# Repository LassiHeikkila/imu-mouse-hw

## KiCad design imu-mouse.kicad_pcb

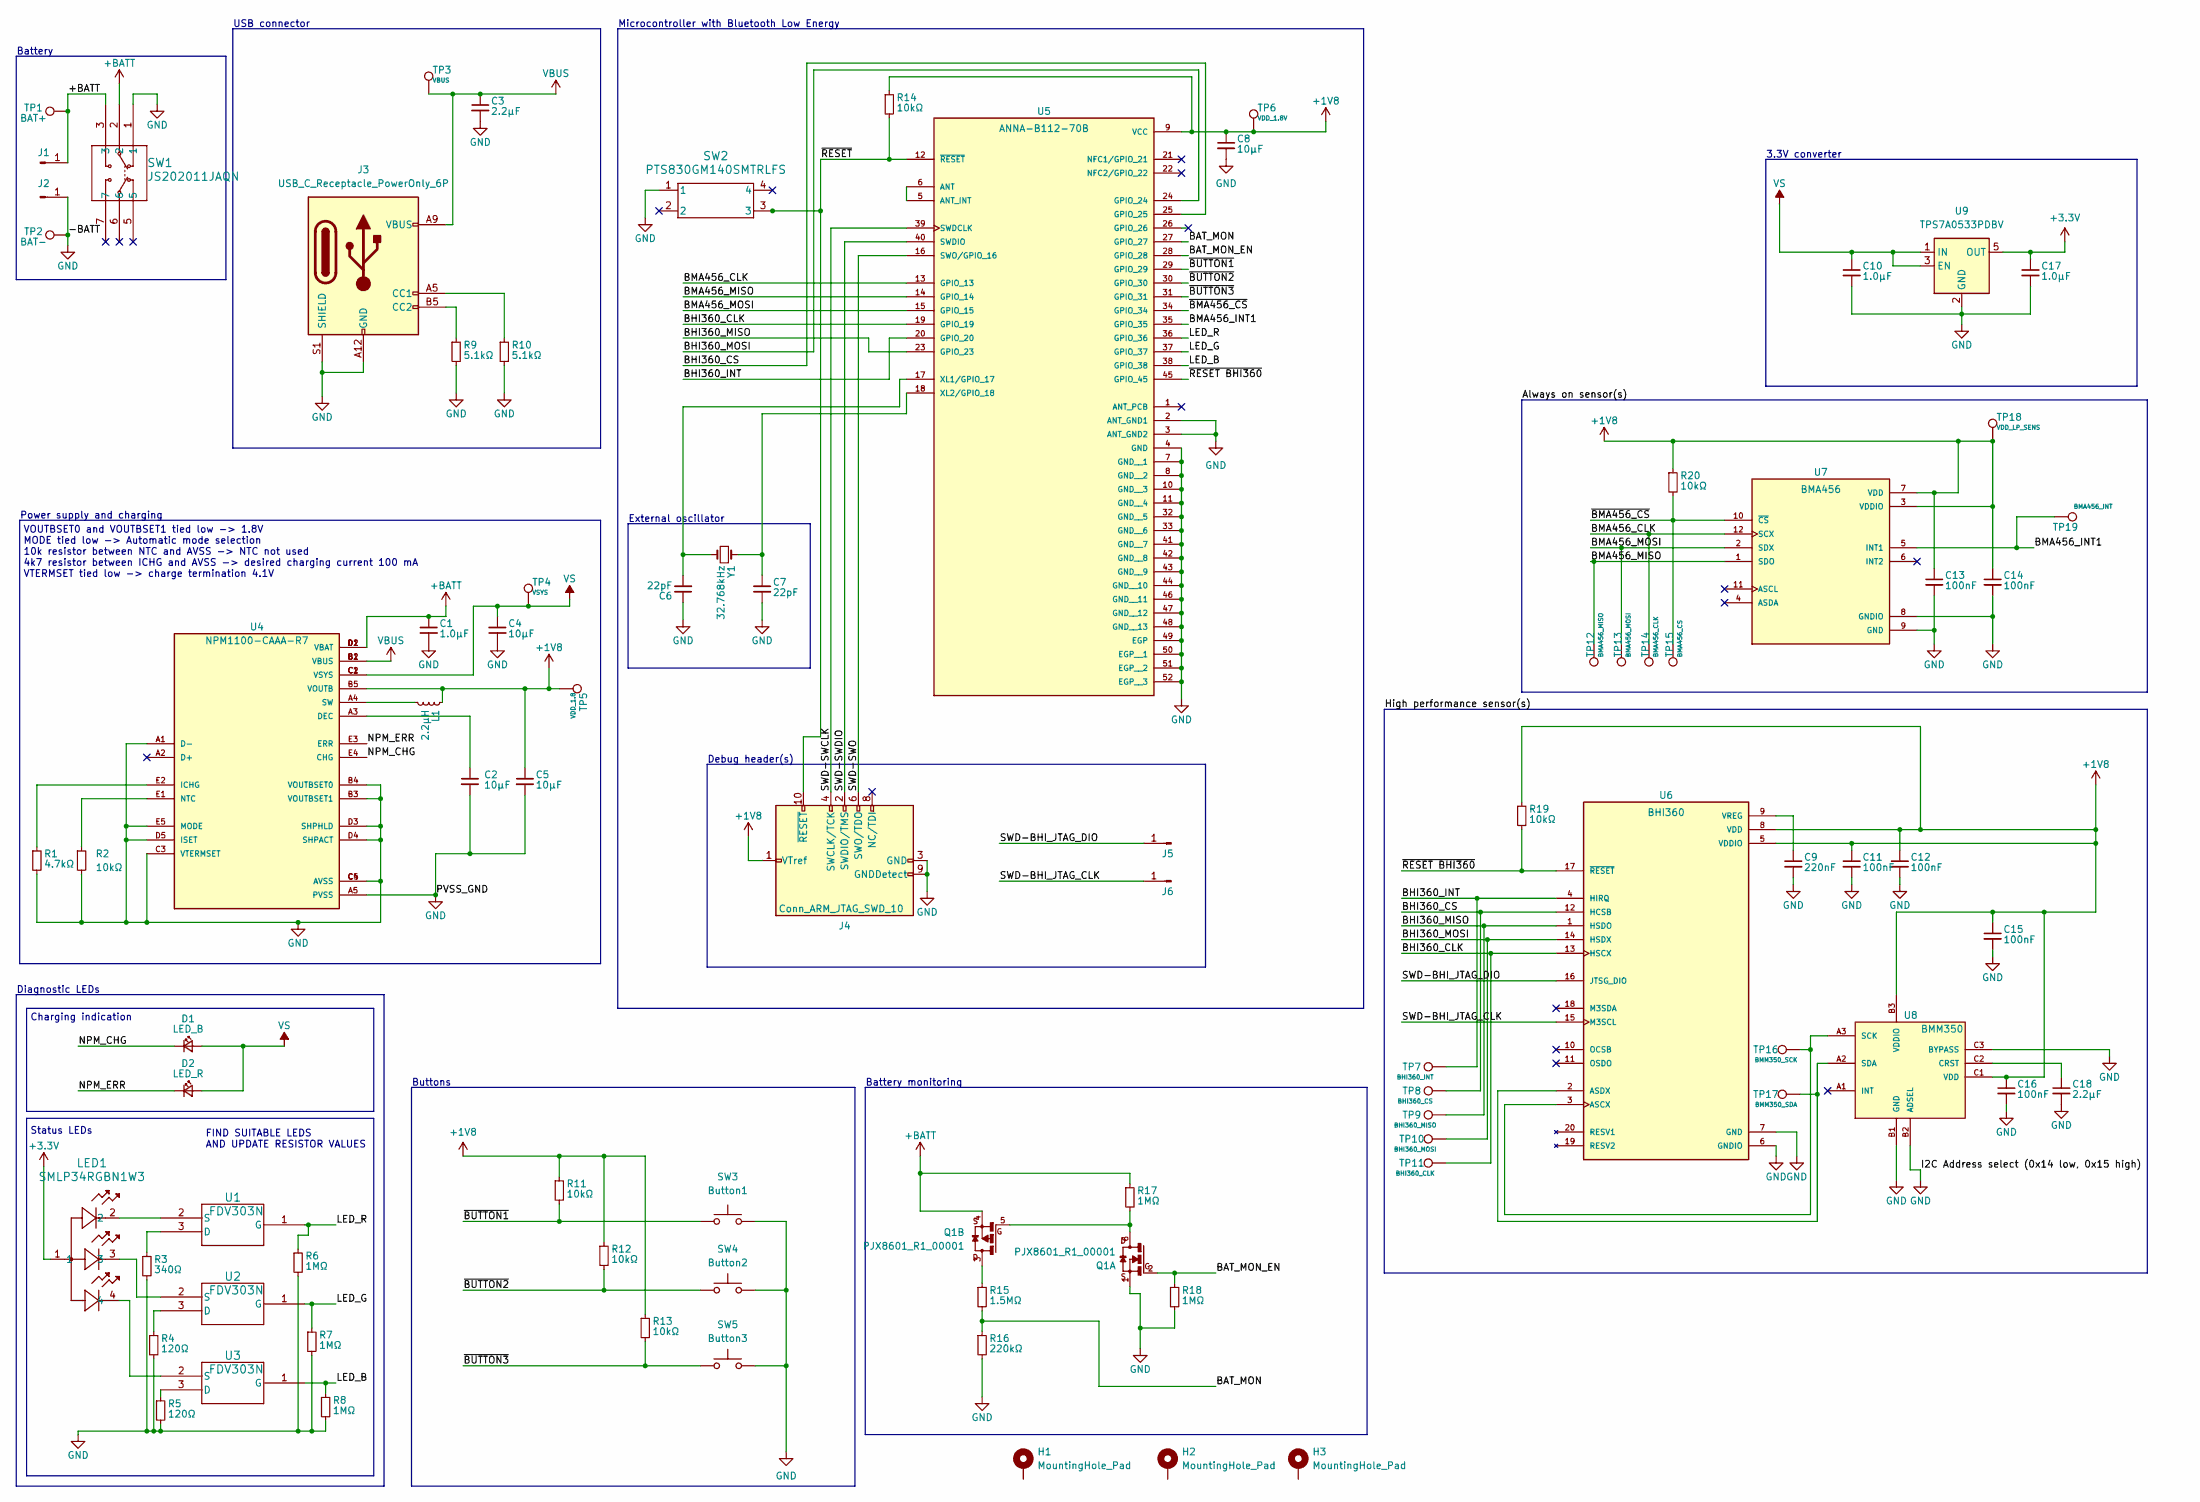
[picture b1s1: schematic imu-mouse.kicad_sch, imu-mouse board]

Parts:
C1, C10, C17: 1.0µF; C_0805_2012Metric; DigiKey_Part_Number CC0805KKX7R8BB105
C2, C4, C5, C8: 10µF; C_0805_2012Metric; DigiKey_Part_Number CC0805KKX7R6BB106
C3, C18: 2.2µF; C_0805_2012Metric; DigiKey_Part_Number CC0805KRX5R7BB225
C6, C7: 22pF; C_0805_2012Metric; DigiKey_Part_Number CC0805KKX7R6BB106
C9: 220nF; C_0805_2012Metric; DigiKey_Part_Number CC0805KRX7R8BB224
C11, C12, C13, C14, C15, C16: 100nF; C_0805_2012Metric; DigiKey_Part_Number CC0805KRX7R9BB104
D1: LED_B; LED_0805_2012Metric; DigiKey_Part_Number 150080BS75000
D2: LED_R; LED_0805_2012Metric; DigiKey_Part_Number 150080RS75000
H1, H2, H3: MountingHole_Pad; MountingHole_3.5mm_Pad
J1, J2, J5, J6: Conn_01x01_Pin; SolderWire-0.1sqmm_1x01_D0.4mm_OD1mm
J3: USB_C_Receptacle_PowerOnly_6P; USB_C_Receptacle_GCT_USB4125-xx-x_6P_TopMnt_Horizontal; DigiKey_Part_Number USB4125-GF-A
J4: Conn_ARM_JTAG_SWD_10; PinHeader_2x05_P1.27mm_Vertical; DigiKey_Part_Number FTSH-105-01-L-DV-007-K
L1: 2.2µH; L_0805_2012Metric; DigiKey_Part_Number dfe201210u-2r2m-p2
LED1: SMLP34RGBN1W3; SMLP34_ROM; DigiKey_Part_Number SMLP34RGBN1W3
Q1: PJX8601_R1_00001; SOT50P160X60-6N; DigiKey_Part_Number PJX8601-R1-00001
R1: 4.7kΩ; R_0805_2012Metric; DigiKey_Part_Number RC0805FR-071K5L
R2, R11, R12, R13, R14, R19, R20: 10kΩ; R_0805_2012Metric; DigiKey_Part_Number RT0805FRE0710KL
R3: 340Ω; R_0805_2012Metric; DigiKey_Part_Number RC0805FR-07330RL
R4, R5: 120Ω; R_0805_2012Metric; DigiKey_Part_Number RT0805FRE07120RL
R6, R7, R8, R17, R18: 1MΩ; R_0805_2012Metric; DigiKey_Part_Number RC0805FR-071ML
R9, R10: 5.1kΩ; R_0805_2012Metric; DigiKey_Part_Number RC0805JR-075K1L
R15: 1.5MΩ; R_0805_2012Metric; DigiKey_Part_Number RT0805FRE071M5L
R16: 220kΩ; R_0805_2012Metric; DigiKey_Part_Number RT0805FRE07220KL
SW1: JS202011JAQN; DigiKey_Part_Number JS202011JAQN
SW2: PTS830GM140SMTRLFS; SWITCH_0SMTRLFS; DigiKey_Part_Number PTS830GM140-SMTR-LFS
SW3: Button1; SW_SPST_PTS645; DigiKey_Part_Number PTS645SL43SMTR92-LFS
SW4: Button2; SW_SPST_PTS645; DigiKey_Part_Number PTS645SL43SMTR92-LFS
SW5: Button3; SW_SPST_PTS645; DigiKey_Part_Number PTS645SL43SMTR92-LFS
TP1: BAT+; TestPoint_Pad_D1.0mm
TP2: BAT-; TestPoint_Pad_D1.0mm
TP3: VBUS; TestPoint_Pad_D1.0mm
TP4: VSYS; TestPoint_Pad_D1.0mm
TP5: VDD_1.8; TestPoint_Pad_D1.0mm
TP6: VDD_1.8V; TestPoint_Pad_D1.0mm
TP7: BHI360_INT; TestPoint_Pad_D1.0mm
TP8: BHI360_CS; TestPoint_Pad_D1.0mm
TP9: BHI360_MISO; TestPoint_Pad_D1.0mm
TP10: BHI360_MOSI; TestPoint_Pad_D1.0mm
TP11: BHI360_CLK; TestPoint_Pad_D1.0mm
TP12: BMA456_MISO; TestPoint_Pad_D1.0mm
TP13: BMA456_MOSI; TestPoint_Pad_D1.0mm
TP14: BMA456_CLK; TestPoint_Pad_D1.0mm
TP15: BMA456_CS; TestPoint_Pad_D1.0mm
TP16: BMM350_SCK; TestPoint_Pad_D1.0mm
TP17: BMM350_SDA; TestPoint_Pad_D1.0mm
TP18: VDD_LP_SENS; TestPoint_Pad_D1.0mm
TP19: BMA456_INT; TestPoint_Pad_D1.0mm
U1, U2, U3: FDV303N; SOT-23-3L_FAS; DigiKey_Part_Number FDV303N
U4: NPM1100-CAAA-R7; BGA25C40P5X5_207X207X52N; DigiKey_Part_Number npm1100-caab-r
U5: ANNA-B112-70B; XCVR_ANNA-B112-70B; DigiKey_Part_Number anna-b112-70b
U6: BHI360; XDCR_BHI360; DigiKey_Part_Number bhi360
U7: BMA456; XDCR_BMA456; DigiKey_Part_Number bma456
U8: BMM350; BGA9C40P3X3_128X128X50; DigiKey_Part_Number BMM350
U9: TPS7A0533PDBV; SOT-23-5; DigiKey_Part_Number TPS7A0533PDBVR
Y1: 32.768kHz; Crystal_SMD_2012-2Pin_2.0x1.2mm; DigiKey_Part_Number FC-12M-32-7680KD-A0

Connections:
+1V8: C5.1, C8.1, C11.1, C12.1, C13.1, C14.1, C15.1, C16.1, J4.1 (VTref), L1.1, R11.1, R12.1, R13.1, R14.1, R19.1, R20.1, TP5.1, TP6.1, TP18.1, U4.B5 (VOUTB), U5.9 (VCC), U6.5 (VDDIO), U6.8 (VDD), U7.3 (VDDIO), U7.7 (VDD), U8.B3 (VDDIO), U8.C1 (VDD); also elsewhere on the board
+3.3V: C17.1, LED1.1, U9.5 (OUT)
+BATT: C1.1, J1.1, Q1.4, R17.1, SW1.2, SW1.3, TP1.1, U4.D1 (VBAT), U4.D2 (VBAT)
/BAT_MON: R15.2, R16.1, U5.27 (GPIO_27); also elsewhere on the board
/BAT_MON_EN: Q1.2, R18.1, U5.28 (GPIO_28); also elsewhere on the board
/BHI360_CLK: TP11.1, U5.19 (GPIO_19), U6.13 (HSCX); also elsewhere on the board
/BHI360_CS: TP8.1, U5.25 (GPIO_25), U6.12 (HCSB); also elsewhere on the board
/BHI360_INT: TP7.1, U5.20 (GPIO_20), U6.4 (HIRQ); also elsewhere on the board
/BHI360_MISO: TP9.1, U5.23 (GPIO_23), U6.1 (HSDO); also elsewhere on the board
/BHI360_MOSI: TP10.1, U5.24 (GPIO_24), U6.14 (HSDX); also elsewhere on the board
/BMA456_CLK: TP14.1, U5.13 (GPIO_13), U7.12 (SCX); also elsewhere on the board
/BMA456_INT1: TP19.1, U5.35 (GPIO_35), U7.5 (INT1); also elsewhere on the board
/BMA456_MISO: TP12.1, U5.14 (GPIO_14), U7.1 (SDO); also elsewhere on the board
/BMA456_MOSI: TP13.1, U5.15 (GPIO_15), U7.2 (SDX); also elsewhere on the board
/LED_B: R8.1, U3.1 (G), U5.38 (GPIO_38); also elsewhere on the board
/LED_G: R7.1, U2.1 (G), U5.37 (GPIO_37); also elsewhere on the board
/LED_R: R6.1, U1.1 (G), U5.36 (GPIO_36); also elsewhere on the board
/NPM_CHG: D1.1 (K), U4.E4 (CHG)
/NPM_ERR: D2.1 (K), U4.E3 (ERR)
/SWD-BHI_JTAG_CLK: J6.1, U6.15 (M3SCL)
/SWD-BHI_JTAG_DIO: J5.1, U6.16 (JTSG_DIO)
/SWD-SWCLK: J4.4 (SWCLK/TCK), U5.39 (SWDCLK); also elsewhere on the board
/SWD-SWDIO: J4.2 (SWDIO/TMS), U5.40 (SWDIO); also elsewhere on the board
/SWD-SWO: J4.6 (SWO/TDO), U5.16 (SWO/GPIO_16); also elsewhere on the board
/~BMA456_CS: R20.2, TP15.1, U5.34 (GPIO_34), U7.10 (~CS); also elsewhere on the board
/~BUTTON1: R11.2, SW3.1, U5.29 (GPIO_29); also elsewhere on the board
/~BUTTON2: R12.2, SW4.1, U5.30 (GPIO_30); also elsewhere on the board
/~BUTTON3: R13.2, SW5.1, U5.31 (GPIO_31); also elsewhere on the board
/~RESET BHI360: R19.2, U5.45 (GPIO_45), U6.17 (~RESET); also elsewhere on the board
/~RESET: J4.10 (~RESET), R14.2, SW2.3, U5.12 (~RESET); also elsewhere on the board
GND: C1.2, C2.2, C3.2, C4.2, C5.2, C6.1, C7.2, C8.2, C9.2, C10.2, C11.2, C12.2, C13.2, C14.2, C15.2, C16.2, C17.2, C18.2, J2.1, J3.A12 (GND), J3.B12 (GND), J3.S1 (SHIELD), J4.3 (GND), J4.5 (GND), J4.9 (GNDDetect), Q1.1, R1.2, R2.2, R3.2, R4.2, R5.2, R6.2, R7.2, R8.2, R9.2, R10.2, R16.2, R18.2, SW1.1, SW2.1, SW3.2, SW4.2, SW5.2, TP2.1, U4.A1 (D-), U4.A5 (PVSS), U4.B3 (VOUTBSET1), U4.B4 (VOUTBSET0), U4.C3 (VTERMSET), U4.C4 (AVSS), U4.C5 (AVSS), U4.D3 (SHPHLD), U4.D4 (SHPACT), U4.D5 (ISET), U4.E5 (MODE), U5.2 (ANT_GND1), U5.3 (ANT_GND2), U5.4 (GND), U5.7 (GND__1), U5.8 (GND__2), U5.10 (GND__3), U5.11 (GND__4), U5.32 (GND__5), U5.33 (GND__6), U5.41 (GND__7), U5.42 (GND__8), U5.43 (GND__9), U5.44 (GND__10), U5.46 (GND__11), U5.47 (GND__12), U5.48 (GND__13), U5.49 (EGP), U5.50 (EGP__1), U5.51 (EGP__2), U5.52 (EGP__3), U6.6 (GNDIO), U6.7 (GND), U7.8 (GNDIO), U7.9 (GND), U8.B1 (GND), U8.B2 (ADSEL), U8.C3 (BYPASS), U9.2 (GND); also elsewhere on the board
unnamed: J3.A5 (CC1), R10.1
unnamed: J3.B5 (CC2), R9.1
unnamed: Q1.3, R15.1
unnamed: Q1.5, Q1.6, R17.2
unnamed: R3.1, U1.3 (D)
unnamed: LED1.2, U1.2 (S)
unnamed: R4.1, U2.3 (D)
unnamed: LED1.3, U2.2 (S)
unnamed: R5.1, U3.3 (D)
unnamed: LED1.4, U3.2 (S)
unnamed: C2.1, U4.A3 (DEC)
unnamed: R1.1, U4.E2 (ICHG)
unnamed: R2.1, U4.E1 (NTC)
unnamed: L1.2, U4.A4 (SW)
unnamed: U5.5 (ANT_INT), U5.6 (ANT)
unnamed 47: C6.2, U5.17 (XL1/GPIO_17), Y1.2; also elsewhere on the board
unnamed 48: C7.1, U5.18 (XL2/GPIO_18), Y1.1; also elsewhere on the board
unnamed: TP16.1, U6.3 (ASCX), U8.A3 (SCK)
unnamed: TP17.1, U6.2 (ASDX), U8.A2 (SDA)
unnamed: C9.1, U6.9 (VREG)
unnamed: C18.1, U8.C2 (CRST)
VBUS: C3.1, J3.A9 (VBUS), J3.B9 (VBUS), TP3.1, U4.B1 (VBUS), U4.B2 (VBUS)
VS: C4.1, C10.1, D1.2 (A), D2.2 (A), TP4.1, U4.C1 (VSYS), U4.C2 (VSYS), U9.1 (IN), U9.3 (EN)

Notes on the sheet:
USB connector
Microcontroller with Bluetooth Low Energy
Power supply and charging
External oscillator
VOUTBSET0 and VOUTBSET1 tied low -> 1.8V MODE tied low -> Automatic mode selection 10k resistor between NTC and AVSS -> NTC not used 4k7 resistor between ICHG and AVSS -> desired charging current 100 mA VTERMSET tied low -> charge termination 4.1V
FIND SUITABLE LEDS AND UPDATE RESISTOR VALUES
Diagnostic LEDs
Debug header(s)
Buttons
Battery monitoring
Status LEDs
Charging indication
Battery
3.3V converter

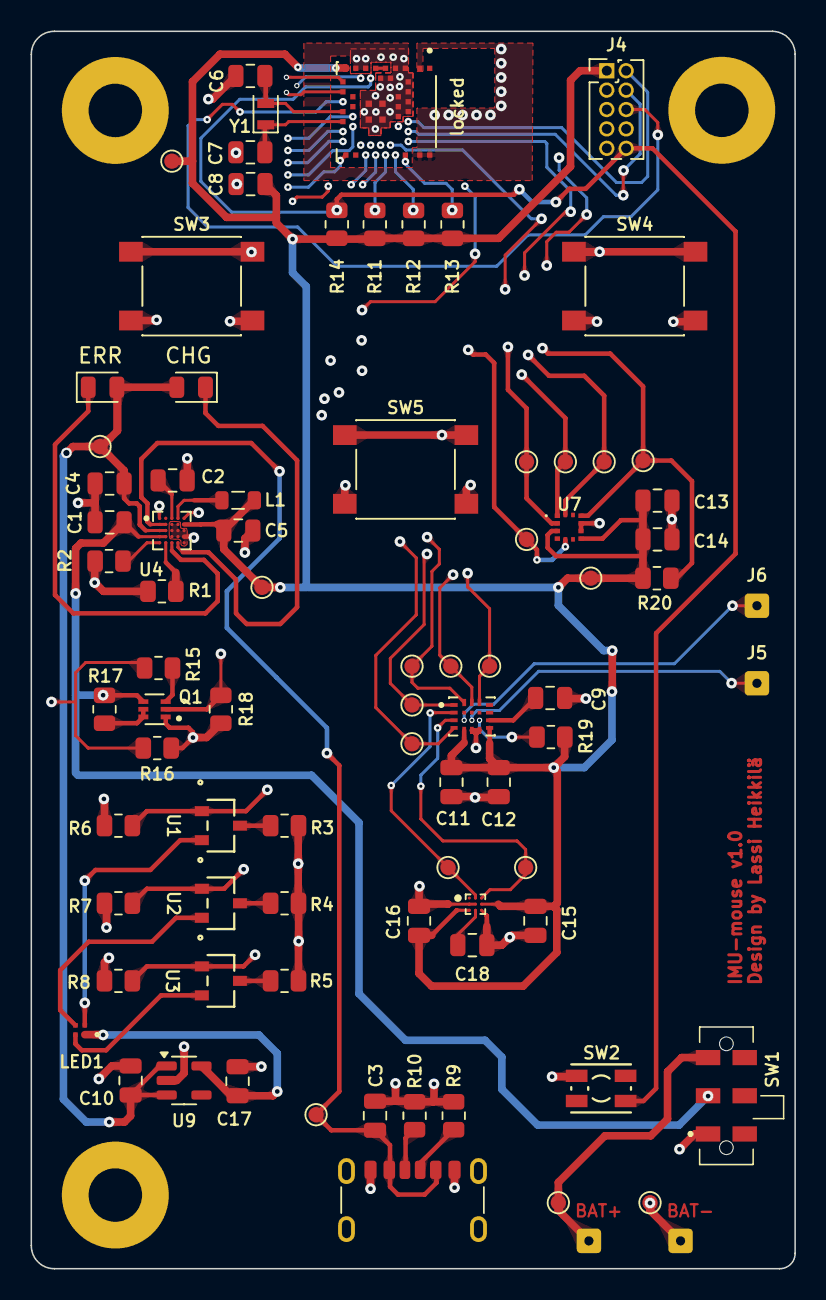
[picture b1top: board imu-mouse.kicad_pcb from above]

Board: 4 copper layers, 50.0 x 81.0 mm, 86 parts (0 on the bottom side), 54 nets.

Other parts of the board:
locked: ANNA-B112-70B; XCVR_ANNA-B112-70B

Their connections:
+1V8: locked.9 (VCC); also elsewhere on the board
/BAT_MON: locked.27 (GPIO_27); also elsewhere on the board
/BAT_MON_EN: locked.28 (GPIO_28); also elsewhere on the board
/BHI360_CLK: locked.19 (GPIO_19); also elsewhere on the board
/BHI360_CS: locked.25 (GPIO_25); also elsewhere on the board
/BHI360_INT: locked.20 (GPIO_20); also elsewhere on the board
/BHI360_MISO: locked.23 (GPIO_23); also elsewhere on the board
/BHI360_MOSI: locked.24 (GPIO_24); also elsewhere on the board
/BMA456_CLK: locked.13 (GPIO_13); also elsewhere on the board
/BMA456_INT1: locked.35 (GPIO_35); also elsewhere on the board
/BMA456_MISO: locked.14 (GPIO_14); also elsewhere on the board
/BMA456_MOSI: locked.15 (GPIO_15); also elsewhere on the board
/LED_B: locked.38 (GPIO_38); also elsewhere on the board
/LED_G: locked.37 (GPIO_37); also elsewhere on the board
/LED_R: locked.36 (GPIO_36); also elsewhere on the board
/SWD-SWCLK: locked.39 (SWDCLK); also elsewhere on the board
/SWD-SWDIO: locked.40 (SWDIO); also elsewhere on the board
/SWD-SWO: locked.16 (SWO/GPIO_16); also elsewhere on the board
/~BMA456_CS: locked.34 (GPIO_34); also elsewhere on the board
/~BUTTON1: locked.29 (GPIO_29); also elsewhere on the board
/~BUTTON2: locked.30 (GPIO_30); also elsewhere on the board
/~BUTTON3: locked.31 (GPIO_31); also elsewhere on the board
/~RESET BHI360: locked.45 (GPIO_45); also elsewhere on the board
/~RESET: locked.12 (~RESET); also elsewhere on the board
GND: locked.2 (ANT_GND1), locked.3 (ANT_GND2), locked.4 (GND), locked.7 (GND__1), locked.8 (GND__2), locked.10 (GND__3), locked.11 (GND__4), locked.32 (GND__5), locked.33 (GND__6), locked.41 (GND__7), locked.42 (GND__8), locked.43 (GND__9), locked.44 (GND__10), locked.46 (GND__11), locked.47 (GND__12), locked.48 (GND__13), locked.49 (EGP), locked.50 (EGP__1), locked.51 (EGP__2), locked.52 (EGP__3); also elsewhere on the board
unnamed: locked.5 (ANT_INT), locked.6 (ANT)
unnamed 47: locked.17 (XL1/GPIO_17); also elsewhere on the board
unnamed 48: locked.18 (XL2/GPIO_18); also elsewhere on the board

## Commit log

2024-06-25 Commit whole KiCad project, v1
